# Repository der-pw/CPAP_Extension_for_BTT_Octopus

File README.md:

# CPAP Extension for BTT Octopus
... and some other boards  

## Extension to add the CPAP function without giving up the Neopixel port.
The WS7040 “CPAP Cooling Controller” requires a positive 5V switching signal to control the speed of the motor. For some boards like the BTT Octopus, the workaround is to use the pin for Neopixel (PB0 or ​​PB10).
But if you don't want to loose out the fancy Neopixel Blinky thing, you can attach this little board to the EXP1 port. In most cases we don't need EXP1 because we have a display connected to the SBC (Raspberry Pi, etc.).

### Pin mapping
I choosed the ports for **BEEPER** and **LCD_RS**.
On the Octopus Pro V1.1 this corresponds to pins `PE8` and `PE10`.
According to the data sheet of the used STM, they can PWM, and that's exactly what we need.

The beeper is additional. Some extra informations via speaker are helpful. :smile:  

Information about the pin mapping on other boards.  
Do you miss one here? Please let me know!  

| Board (Version)  | Description | Mapping new | PIN
| ---              | ---         | ---         | :---: |
| BTT Octopus Pro V1.1 | *STM32H723ZET6*|            |       |
|                  | BEEPER      | BUZZER      | `PE8`  |
|                  | LCD_RS      | CPAP Control| `PE10`  |
| BTT Octopus V1.0     | *STM32F446ZET6*|            |       |
|                  | BEEPER      | BUZZER      | `PE8`   |
|                  | LCD_RS      | CPAP Control| `PE10`  |
| Fysetc Cheetah V3.0 (EXP3)    | *STM32F446RCT6* |            |       |
|                  | BEEP        | BUZZER      | `PB10`   |
|                  | LCD_RS      | CPAP Control| `PB14`  |

### Parts
| Position | Description | Value      | Information
| ---      | ---         | ---        | ---
| R1       | Resistor    | 4.7k       | SMD 0805
| U1       | Buffer Gate | 74LVC1G125 | https://www.ti.com/lit/ds/symlink/sn74lvc1g125.pdf
| J1       | IDC Connector for EXP1 | SFH11-PBPC-D05-ST-BK | https://www.digikey.com/de/products/detail/sullins-connector-solutions/SFH11-PBPC-D05-ST-BK/1990087
| J2       | JST XH male | pitch 2.54 | https://de.aliexpress.com/item/1005003422202370.html
| optional |             |            |just if you want the buzzer
| R2       | Resistor    | 330        | SMD 0805
| R3       | Resistor    | 4.7K / 10k | SMD 0805
| Q1       | N-MOSFET    | AO4300A    | SOT-23
| BZ1      | Buzzer (passive) | 12x8.5mm  6.6mm Pitch | https://www.amazon.de/dp/B0179I6LIK 

All SMD parts are specified in the production file. I have no experience with assembling THT parts via the SMT service, so I always solder them by hand. In this case this applies to the buzzer, the JST connector and the IDC connector.

U1 buffer gate is the same level shifter as the one in the Octopus Board. The IDC Connector J1 is hard to find. Sometimes it's available at aliexpress, or you have a friendly Guy, he can order at digikey.
A 2x5 (2.54mm) pin header will also work, but please be aware to check the direction if you put it in your board.

### Place the addon into your board
Here you can see where the addon is located on the BTT Octopus Pro.  

### Connection to controller board
Connect the + pin from the expansion board to the VSR pin from the controller (Pin 2).
In addition, the - pin with the GND pin (Pin 3), even if it is not absolutely necessary.

### Klipper config
I've set the cycle time to 0.00004 (25 kHz.) This is how I got the best results and can set the power down to 6%.

```
[fan]
pin: PE10
max_power: 1.0
kick_start_time: 0.1
cycle_time: 0.00004 #25kHz
hardware_pwm: False
off_below: 0.06
```

### Additional buzzer function
Please check the configuration file in *klipper* folder.
You can copy the *macro_buzzer.cfg* into your configuration folder and include it in your *printer.cfg* with `[include macro_buzzer.cfg]`.
Enable the correct pin depending on your board.
Now you will get some tones about `M300`.
For example, you can use `M300 S440 P1000` to play a tone at 440 Hz for 1 second. In *macro_buzzer.cfg* you'll find some macros that play small melodies.

### Resistor for the buzzer
I have added a resistor in series to the buzzer with 10Ω to reduce resonances in some fequencies. If you need it louder or quieter, you can chance R4 with other values.

### FAQ
*Why not to connect to one of the many FAN ports?*  
The fan ports are controlled by a N-channel MOSFET. You just can controll the negative side with PWM but you need the positive side, because the VSR input has common GND.

*Why not to connect to the GPIO of my Raspberry Pi?*  
It's the same like at some pins of your Octopus Board. They just have a logic level of 3.3V. The VSR Input of the CPAP controller needs 5V for 100% cooling power. You lose around 30%.

*Does this also work with other boards?*  
So far I have only tested it with the Octopus, Octopus Pro and the Fysetc Cheetah 3.0. It should work with many boards that offer a slot for a 12864 display. However, you then have to check whether a pin with a PWM signal arrives at the positions I used.

--- 

### This is Open Source Hardware

Feel free to create your own modifiactions and versions!

Gerbers are made with [Fabrication Toolkit](https://github.com/bennymeg/JLC-Plugin-for-KiCad).

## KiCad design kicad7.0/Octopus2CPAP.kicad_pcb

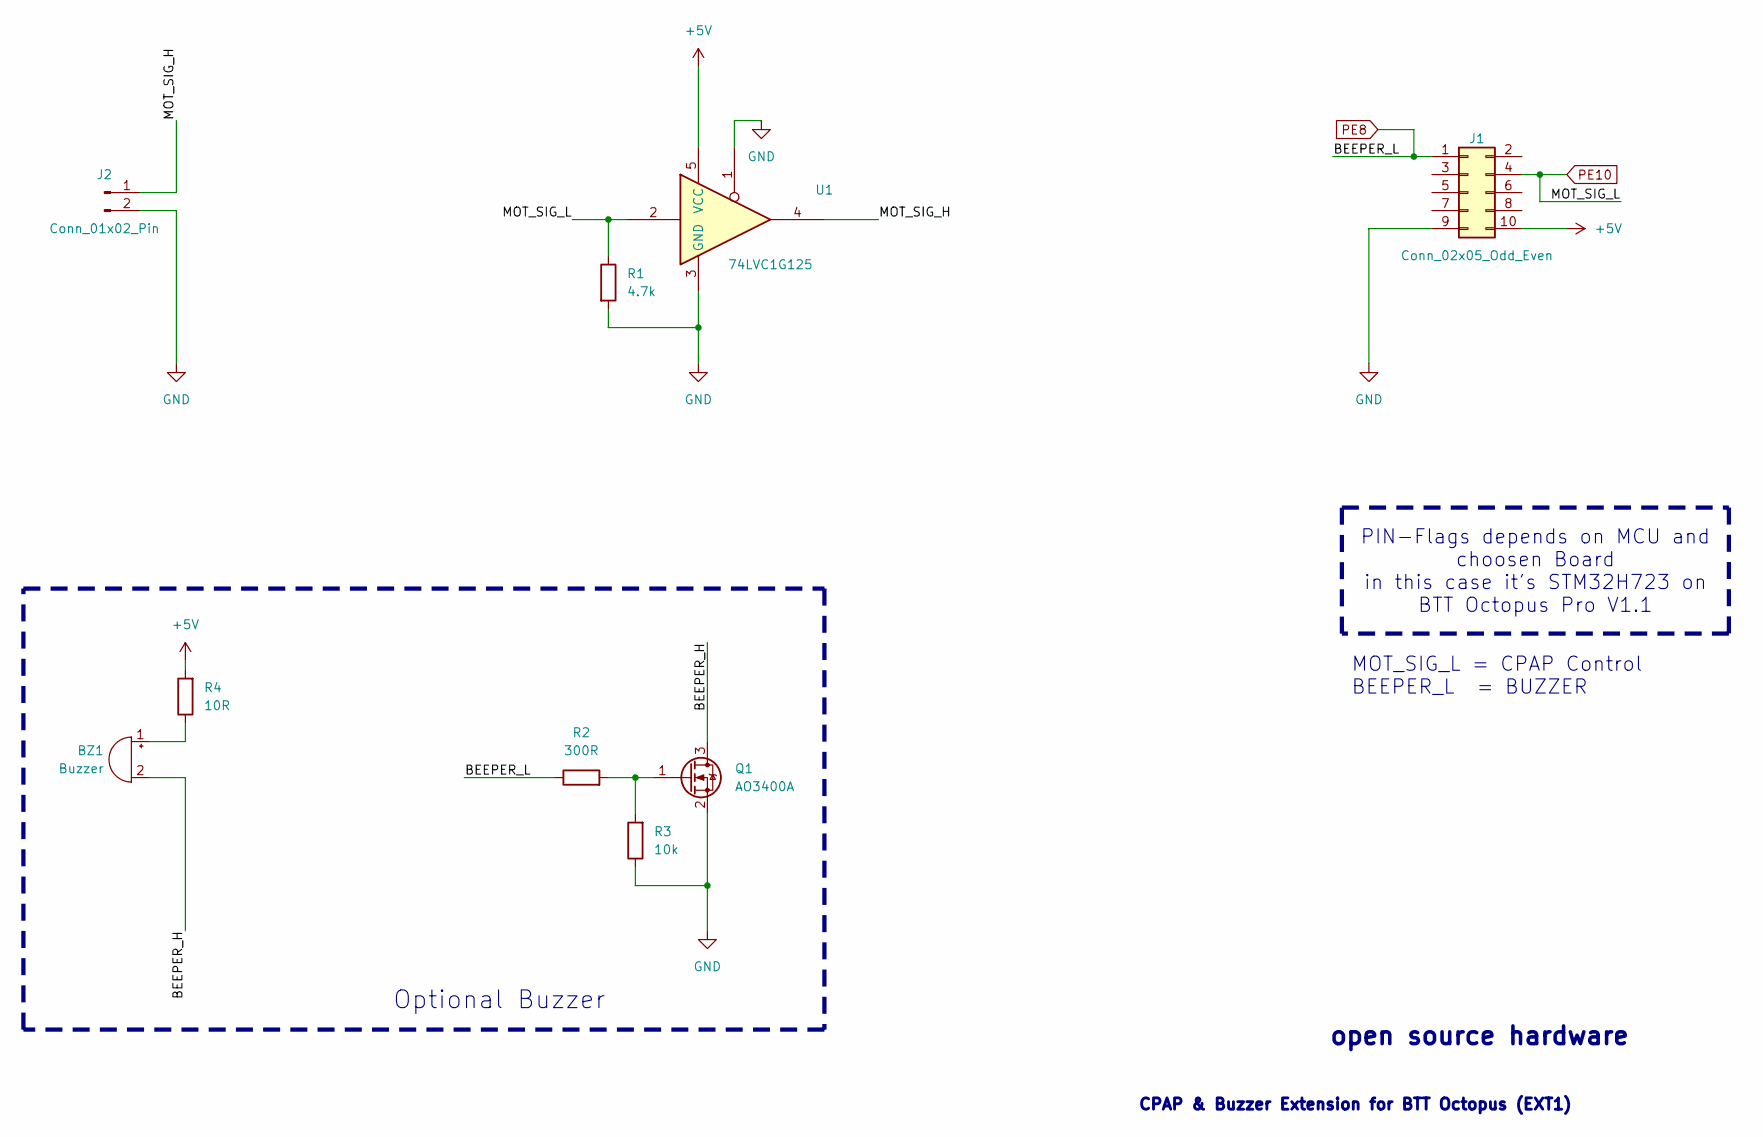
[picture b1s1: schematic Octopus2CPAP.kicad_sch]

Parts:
BZ1: Buzzer; Buzzer_12x9.5RM7.6
J1: Conn_02x05_Odd_Even; PinSocket_2x05_P2.54mm_Vertical
J2: Conn_01x02_Pin; JST_XH_B2B-XH-A_1x02_P2.50mm_Vertical
Q1: AO3400A; SOT-23; MPN C20917; JLCPCB Rotation Offset 180
R1: 4.7k; R_0805_2012Metric_Pad1.20x1.40mm_HandSolder; MPN C17673
R2: 300R; R_0805_2012Metric_Pad1.20x1.40mm_HandSolder; MPN C17617
R3: 10k; R_0805_2012Metric_Pad1.20x1.40mm_HandSolder; MPN C17414
R4: 10R; R_0805_2012Metric_Pad1.20x1.40mm_HandSolder; MPN C17415
U1: 74LVC1G125; SOT-23-5_HandSoldering; MPN C23654; JLCPCB Rotation Offset -90

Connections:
+5V: J1.10, R4.2, U1.5 (VCC)
/BEEPER_H: BZ1.2 (+), Q1.3 (D)
/MOT_SIG_H: J2.1, U1.4
GND: J1.9, J2.2, Q1.2 (S), R1.2, R3.1, U1.1, U1.3 (GND)
unnamed: BZ1.1 (-), R4.1
unnamed: Q1.1 (G), R2.2, R3.2
PE8: J1.1, R2.1
PE10: J1.4, R1.1, U1.2

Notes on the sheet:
PIN-Flags depends on MCU and choosen Board in this case it's STM32H723 on BTT Octopus Pro V1.1
MOT_SIG_L = CPAP Control BEEPER_L = BUZZER
open source hardware
Optional Buzzer
CPAP & Buzzer Extension for BTT Octopus (EXT1)

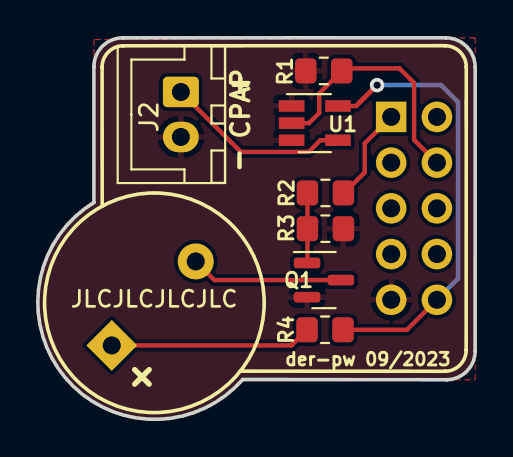
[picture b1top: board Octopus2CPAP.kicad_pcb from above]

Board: 2 copper layers, 24.3 x 21.2 mm, 9 parts (1 on the bottom side), 8 nets.

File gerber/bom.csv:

Designator,Footprint,Quantity,Value,LCSC Part #
Q1,SOT-23,1,AO3400A,C20917
R1,0805,1,4.7k,C17673
R2,0805,1,300R,C17617
R3,0805,1,10k,C17414
R4,0805,1,10R,C17415
U1,SOT-23-5_HandSoldering,1,74LVC1G125,C23654

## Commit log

2023-09-04 initial upload
2023-09-05 some changes at pcb
2023-09-05 update gerber
2023-09-30 finalize board
2023-10-08 finalize and release
2023-10-08 add some faq informations
2023-10-08 add some FAQ notes
2023-10-08 fixed small typos
2024-02-17 Update macro_buzzer.cfg
    change output_pin to pwm_cycle_pin
2025-01-19 Update README.md
    added pin location
